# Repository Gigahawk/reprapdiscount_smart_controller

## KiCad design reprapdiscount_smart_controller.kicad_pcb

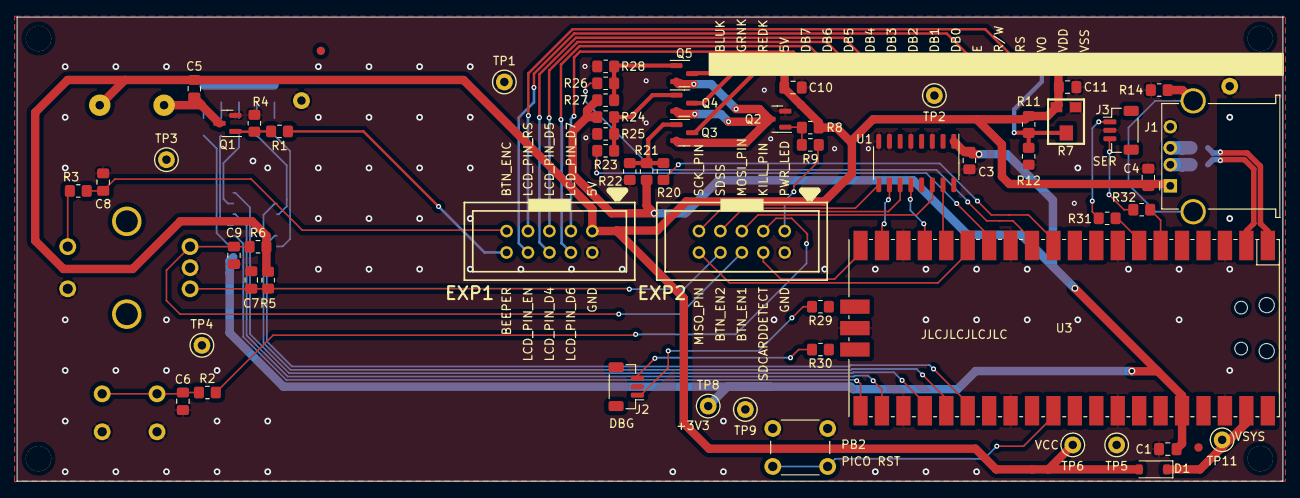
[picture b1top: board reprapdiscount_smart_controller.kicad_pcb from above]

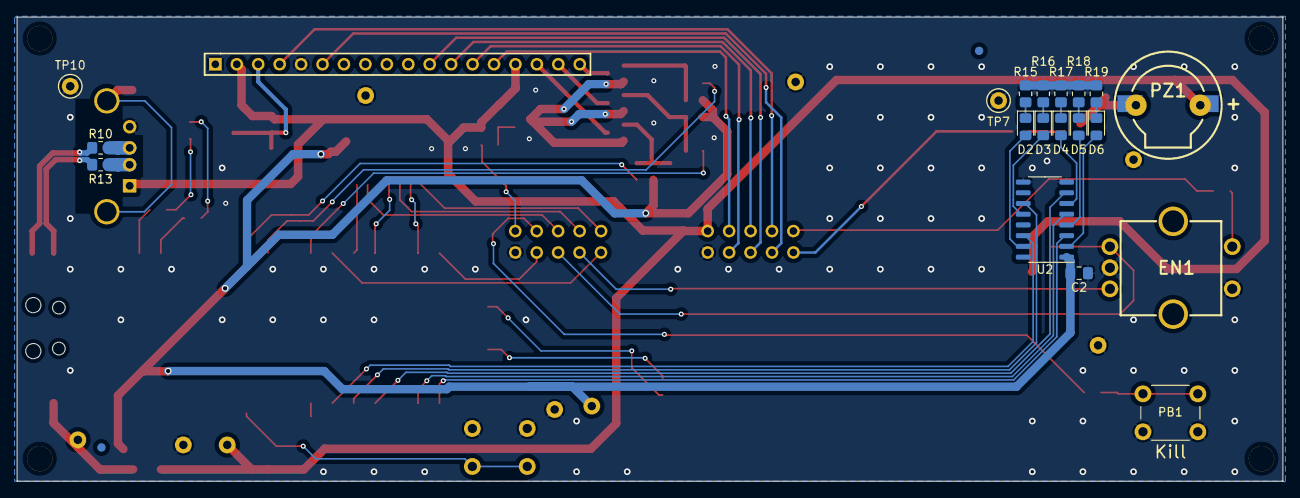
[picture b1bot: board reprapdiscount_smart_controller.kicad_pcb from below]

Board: 2 copper layers, 150.0 x 55.0 mm, 87 parts (23 on the bottom side), 69 nets.

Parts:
C1, C4, C10, C11: 10u; C_0805_2012Metric_Pad1.18x1.45mm_HandSolder
C2, C3, C5, C6, C7, C8, C9: 100n; C_0805_2012Metric_Pad1.18x1.45mm_HandSolder
D1: MBR120; D_SOD-123
D2: RED; LED_0805_2012Metric_Pad1.15x1.40mm_HandSolder
D3: GRN; LED_0805_2012Metric_Pad1.15x1.40mm_HandSolder
D4: BLU; LED_0805_2012Metric_Pad1.15x1.40mm_HandSolder
D5: YLW; LED_0805_2012Metric_Pad1.15x1.40mm_HandSolder
D6: WHT; LED_0805_2012Metric_Pad1.15x1.40mm_HandSolder
EN1: BC111E5244B2; ROTARY ENCODER
EXP1, EXP2: Header 5X2; HDR2X5_EXP
FID1, FID2, FID3, FID4: Fiducial; Fiducial_1mm_Mask2mm
H1, H2, H3, H4: MountingHole; MountingHole_3mm
J1: USB_A; USB_A_Stewart_SS-52100-001_Horizontal
J2, J3: Conn_01x03_Pin; JST_SH_BM03B-SRSS-TB_1x03-1MP_P1.00mm_Vertical
LCD1: Character lcd; HDR1X18
PB1: STOP; SW_PUSH_6mm_H7.3mm
PB2: PICO RST; SW_PUSH_6mm_H7.3mm
PZ1: PIEZO; PIEZO 11MM
Q1, Q2, Q3, Q4, Q5: DMN2005K-7; SOT-23
R1, R4, R9, R14, R20, R23, R26: 0R; R_0805_2012Metric_Pad1.20x1.40mm_HandSolder
R2: 1k; R_0805_2012Metric_Pad1.20x1.40mm_HandSolder
R3, R29, R30, R31, R32: 100R; R_0805_2012Metric_Pad1.20x1.40mm_HandSolder
R5, R6: 5.1k; R_0805_2012Metric_Pad1.20x1.40mm_HandSolder
R7: 1.4k; RES TRIMPOT
R8, R21, R22, R24, R25, R27, R28: 10k; R_0805_2012Metric_Pad1.20x1.40mm_HandSolder
R10, R13: 22R; R_0805_2012Metric_Pad1.20x1.40mm_HandSolder
R11: DNI; R_0805_2012Metric_Pad1.20x1.40mm_HandSolder
R12: 470R; R_0805_2012Metric_Pad1.20x1.40mm_HandSolder
R15, R16, R18: 91R; R_0805_2012Metric_Pad1.20x1.40mm_HandSolder
R17, R19: 33R; R_0805_2012Metric_Pad1.20x1.40mm_HandSolder
SYM1: Logo_Open_Hardware_Large; OSHW-Logo2_9.8x8mm_Mask
TP1, TP2, TP3, TP4, TP5, TP6, TP7, TP8, TP9, TP10, TP11: TestPoint; TestPoint_Keystone_5000-5004_Miniature
U1, U2: 74HC4050; SO-16_3.9x9.9mm_P1.27mm
U3: Pico; RPi_Pico_SMD_NO_SILK

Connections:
+3V3: C1.2, C2.2, C3.2, R21.2, R24.2, R27.2, TP8.1, U1.1 (+), U2.1 (+), U3.36 (3V3)
BEEPER: EXP1.1, R1.2
BLUK: LCD1.18 (BLUK-), Q5.3 (D)
BTN_EN1: C9.1, EN1.1, EXP2.5, R6.1
BTN_EN2: C7.2, EN1.3, EXP2.3, R5.1
BTN_ENC: C8.2, EXP1.2, R3.1
CONN_D+: J1.3 (D+), R10.2
CONN_D-: J1.2 (D-), R13.2
DBG_RX: R31.1, U3.7 (GPIO5)
DBG_TX: R32.1, U3.6 (GPIO4)
GND: C1.1, C2.1, C3.1, C4.1, C6.1, C7.1, C8.1, C9.2, C10.1, C11.1, EN1.2, EN1.4, EXP1.9, EXP2.9, J1.4 (GND), J2.2, J3.2, LCD1.1 (GND), LCD1.5 (R/W), PB1.2, PB2.2, Q1.2 (S), Q2.2 (S), R4.2, R7.1, R12.2, R14.2, R15.1, R16.1, R17.1, R18.1, R19.1, R22.1, R25.1, R28.1, TP1.1, TP2.1, TP3.1, TP4.1, TP5.1, TP7.1, TP9.1, TP10.1, U1.3, U1.5, U1.7, U1.8 (G), U2.8 (G), U2.9, U3.3 (GND), U3.8 (GND), U3.13 (GND), U3.18 (GND), U3.23 (GND), U3.28 (GND), U3.33 (AGND), U3.38 (GND), U3.42 (GND)
GRNK: LCD1.17 (GRNK-), Q4.3 (D)
HOST_CS: EXP2.4, U1.11
HOST_MOSI: EXP2.6, U1.14
HOST_SCK: EXP2.2, U1.9
LCD4: EXP1.5, LCD1.11 (D4)
LCD5: EXP1.6, LCD1.12 (D5)
LCD6: EXP1.7, LCD1.13 (D6)
LCD7: EXP1.8, LCD1.14 (D7)
LCDE: EXP1.3, LCD1.6 (E)
LCDRS: EXP1.4, LCD1.4 (RS)
LED1: U2.14, U3.26 (GPIO20)
LED2: U2.11, U3.25 (GPIO19)
LED3: U2.7, U3.24 (GPIO18)
LED4: U2.5, U3.22 (GPIO17)
LED5: U2.3, U3.21 (GPIO16)
LEDB: R26.2, U3.12 (GPIO9)
LEDG: R23.2, U3.14 (GPIO10)
LEDK: Q2.3 (D), Q3.2 (S), Q4.2 (S), Q5.2 (S)
LEDR: R20.2, U3.11 (GPIO8)
unnamed: C6.2, PB1.1, R2.1
unnamed: D2.2 (A), U2.15
unnamed: D2.1 (K), R15.2
unnamed: D3.2 (A), U2.12
unnamed: D3.1 (K), R16.2
unnamed: D4.2 (A), U2.6
unnamed: D4.1 (K), R17.2
unnamed: D5.2 (A), U2.4
unnamed: D5.1 (K), R18.2
unnamed: D6.2 (A), U2.2
unnamed: D6.1 (K), R19.2
unnamed: EN1.5, R3.2
unnamed: J1.5 (Shield), R14.1
unnamed: J2.1, R29.2
unnamed: J2.3, R30.2
unnamed: J3.1, R31.2
unnamed: J3.3, R32.2
unnamed: LCD1.3 (Vo), R7.2, R11.2, R12.1
unnamed: C5.1, PZ1.2 (+), Q1.3 (D)
unnamed: Q1.1 (G), R1.1, R4.1
unnamed: Q2.1 (G), R8.1, R9.1
unnamed: Q3.1 (G), R20.1, R21.1, R22.2
unnamed: Q4.1 (G), R23.1, R24.1, R25.2
unnamed: Q5.1 (G), R26.1, R27.1, R28.2
PICO_RST: PB2.1, U3.30 (RUN)
PWR_LED: EXP2.10, R9.2
REDK: LCD1.16 (REDK-), Q3.3 (D)
RESET: EXP2.8, R2.2
SD_CS: U1.12, U3.17 (GPIO13)
SD_DET: EXP2.7, U3.20 (GPIO15)
SD_MISO: EXP2.1, U3.15 (GPIO11)
SD_MOSI: U1.15, U3.16 (GPIO12)
SD_SCK: U1.10, U3.19 (GPIO14)
SWCLK: R29.1, U3.41 (SWCLK)
SWDIO: R30.1, U3.43 (SWDIO)
USB_D+: R10.1, U3.1 (GPIO0)
USB_D-: R13.1, U3.2 (GPIO1)
VCC: C4.2, C5.2, C10.2, C11.2, D1.2 (A), EXP1.10, J1.1 (VBUS), LCD1.2 (Vcc), LCD1.15 (A+), PZ1.1 (-), R5.2, R6.2, R7.3, R8.2, R11.1, TP6.1
VSYS: D1.1 (K), TP11.1, U3.39 (VSYS)

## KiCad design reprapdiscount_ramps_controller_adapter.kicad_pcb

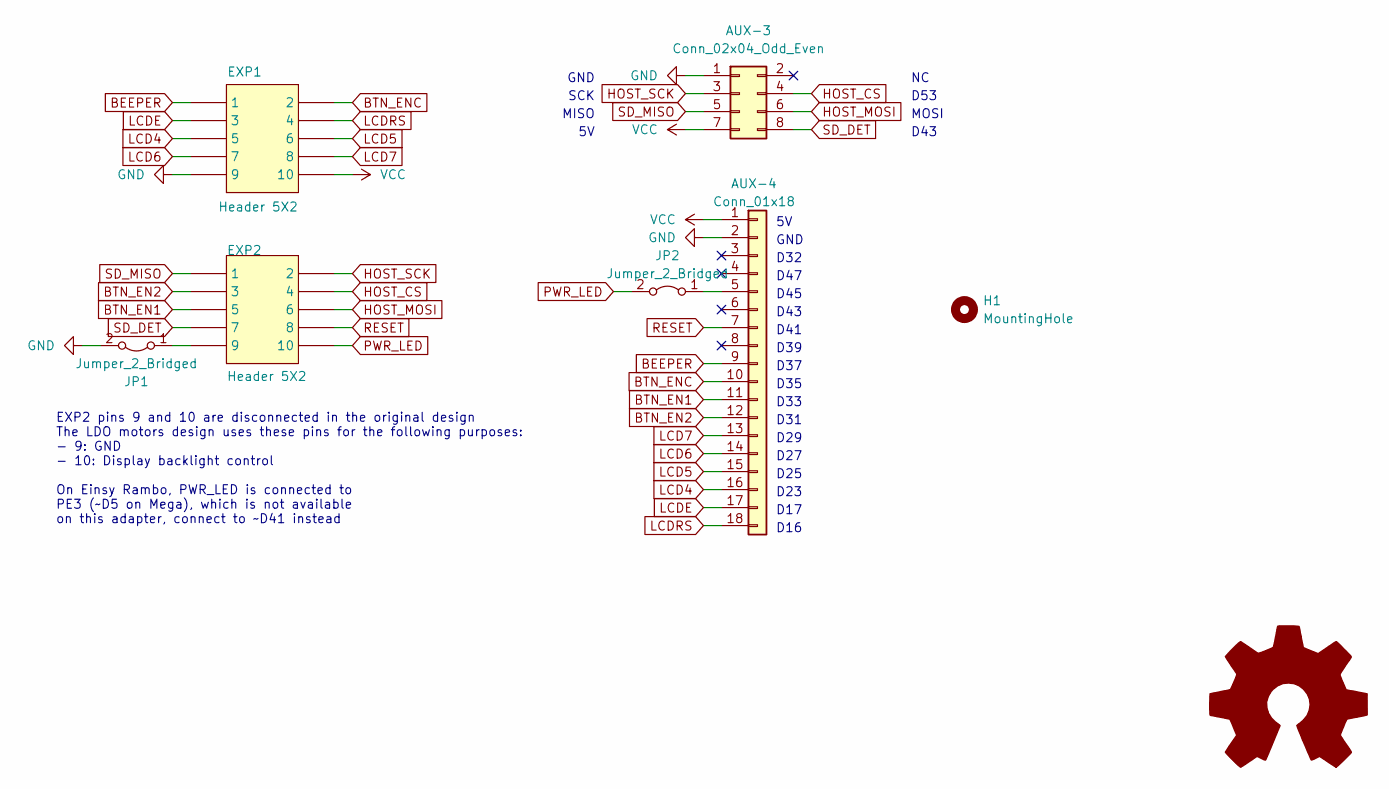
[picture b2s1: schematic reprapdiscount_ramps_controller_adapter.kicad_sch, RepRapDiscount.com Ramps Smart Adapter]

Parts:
AUX-3: Conn_02x04_Odd_Even; PinSocket_2x04_P2.54mm_Vertical_Flipped
AUX-4: Conn_01x18; PinSocket_1x18_P2.54mm_Vertical
EXP1, EXP2: Header 5X2; PinHeader_2x05_P2.54mm_Vertical; Digikey 1175-1627-ND
H1: MountingHole; MountingHole_3.7mm
JP1, JP2: Jumper_2_Bridged; SolderJumper-2_P1.3mm_Bridged_RoundedPad1.0x1.5mm
SYM1: Logo_Open_Hardware_Large; OSHW-Logo2_7.3x6mm_Mask

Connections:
BEEPER: AUX-4.9, EXP1.1
BTN_EN1: AUX-4.11, EXP2.5
BTN_EN2: AUX-4.12, EXP2.3
BTN_ENC: AUX-4.10, EXP1.2
GND: AUX-3.1, AUX-4.2, EXP1.9, JP1.2 (B)
HOST_CS: AUX-3.4, EXP2.4
HOST_MOSI: AUX-3.6, EXP2.6
HOST_SCK: AUX-3.3, EXP2.2
LCD4: AUX-4.16, EXP1.5
LCD5: AUX-4.15, EXP1.6
LCD6: AUX-4.14, EXP1.7
LCD7: AUX-4.13, EXP1.8
LCDE: AUX-4.17, EXP1.3
LCDRS: AUX-4.18, EXP1.4
unnamed: AUX-4.5, JP2.1 (A)
unnamed: EXP2.9, JP1.1 (A)
PWR_LED: EXP2.10, JP2.2 (B)
RESET: AUX-4.7, EXP2.8
SD_DET: AUX-3.8, EXP2.7
SD_MISO: AUX-3.5, EXP2.1
VCC: AUX-3.7, AUX-4.1, EXP1.10

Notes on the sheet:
D27
D45
D17
EXP2 pins 9 and 10 are disconnected in the original design The LDO motors design uses these pins for the following purposes: - 9: GND - 10: Display backlight control On Einsy Rambo, PWR_LED is connected to PE3 (~D5 on Mega), which is not available on this adapter, connect to ~D41 instead
D32
D37
D35
GND
D23
D43
D53
D47
MOSI
D25
D31
D16
MISO
SCK
D39
D33
D29
D41

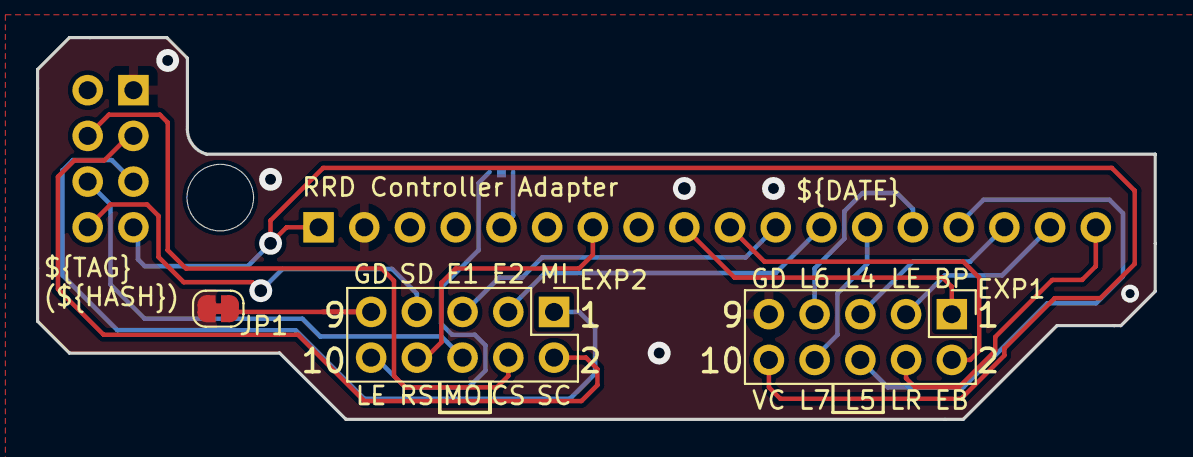
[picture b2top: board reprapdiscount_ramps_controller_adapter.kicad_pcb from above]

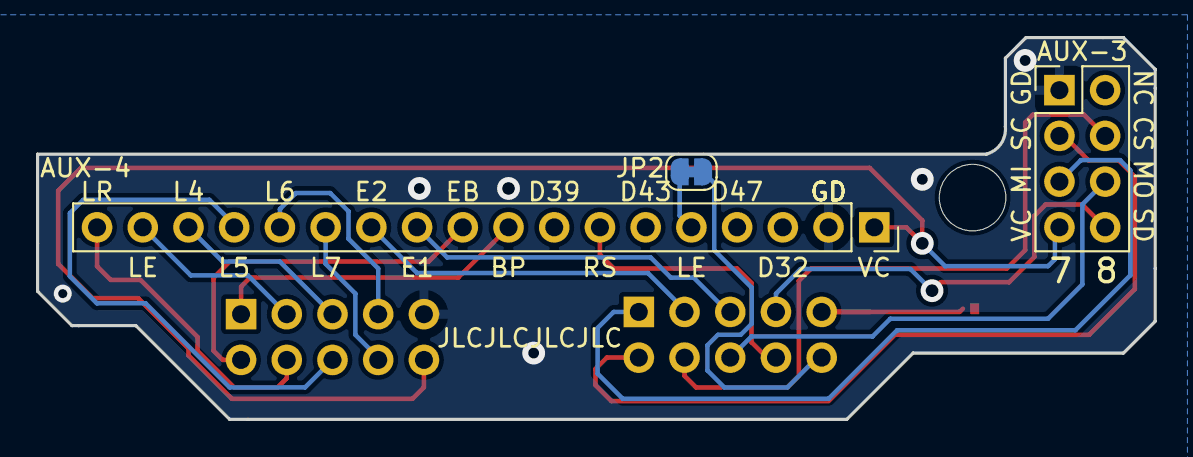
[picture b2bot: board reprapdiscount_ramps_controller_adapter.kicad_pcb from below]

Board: 2 copper layers, 62.1 x 21.2 mm, 8 parts (3 on the bottom side), 21 nets.

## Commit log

2023-08-28 import original altium project files
2023-08-28 rename files
2023-08-28 convert altium files to kicad
2023-08-28 generate footprint library from layout
2023-08-28 fixup: fix schematic and layout references
    - replace random 3V3 pth footprints with vias
2023-08-28 fixup: switch to global net names
2023-08-28 fixup: switch to kicad native passive symbols
    - redo fill, cleanup broken connections
2023-08-29 fixup: add all missing 3d models
2023-09-01 ci: add ci script
2023-09-05 fixup: switch layer names to standard kicad names
2023-09-05 fixup: specify component types in footprint lib
2023-09-07 fixup: restore mounting holes lost during cleanup
2023-09-12 fixup: fix reset button height
2023-09-12 feature: add parts from ldo-rrlcd-a007
2023-09-12 feature: add fiducials
2023-09-13 silkscreen: update to match ldo-rrlcd-a007
2023-09-13 feature: add back side fiducials
2023-09-13 feature: add stitching vias
2023-09-19 feature: add revision info to builds
2023-09-19 schem: use template with more room for revision info
2023-09-19 bugfix: switch REVISION var to HASH
    Fixes some conflict in the layout
2023-09-19 feature: redesign for usb host functionality
2023-09-19 feature: add order number location
2023-09-19 layout: remove copper fill around bottom side usb traces
2023-09-19 layout: slight adjustments to layout
2023-09-19 layout: minor fixes and adjustments
2023-09-20 feature: add status leds to pico
2023-09-20 ci: export bom
2023-09-22 feature: use buffer to drive leds
2023-09-22 bom: specify digikey part numbers
2023-09-25 feature: support adafruit rgb display
2023-09-25 feature: add pico debug connections, testpoints
2023-09-25 bom: update bom
2023-09-25 cleanup: remove vias blocking silkscreen
2023-09-26 schem: export revision info to all sheets
2023-09-26 schem: fix page numbering
2023-10-03 adapter: add adapter based on released gerbers
2023-10-03 adapter: finish routing
2023-10-03 adapter: update silkscreen
2023-10-03 adapter: clean up schematic
2023-10-03 adapter: setup ci
2023-10-03 adapter: add ldo connections
    - adapter: update silkscreen
2023-10-03 adapter: adjust routing
2023-10-03 adapter: minor layout and silk adjustments
2023-10-03 adapter: minor track adjustments
2023-10-03 adapter: move revision info silk
2023-10-04 all: add oshw logo to design
